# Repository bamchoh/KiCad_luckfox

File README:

# Luckfox Extension Board (KiCad Project)

This repository contains the KiCad project files for the Luckfox extension board. The Luckfox board is an expansion board for the SoB (System on Board) platform.

## Features

- Designed using KiCad.
- Provides 5V power supply via USB port.
- Suitable for expanding the capabilities of the Luckfox SoB.

## Directory Structure

- `.kicad_pcb`, `.kicad_sch`, `.kicad_pro`: Main KiCad project files.
- `production/`: Contains BOM, netlist, positions, and production backups.
- `luckfox-backups/`: Automatic and manual project backups.

## Getting Started

1. Open the project in KiCad.
2. Review the schematic and PCB layout.
3. Use the files in the `production/` directory for manufacturing and assembly.

## License

Please specify your license here.

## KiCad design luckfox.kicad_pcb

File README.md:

# Luckfox Extension Board (KiCad Project)

This repository contains the KiCad project files for the Luckfox extension board. The Luckfox board is an expansion board for the SoB (System on Board) platform.

## Features

- Designed using KiCad.
- Provides 5V power supply via USB port.
- Suitable for expanding the capabilities of the Luckfox SoB.

## Directory Structure

- `.kicad_pcb`, `.kicad_sch`, `.kicad_pro`: Main KiCad project files.

## Getting Started

1. Open the project in KiCad.
2. Review the schematic and PCB layout.

## License

Please specify your license here.

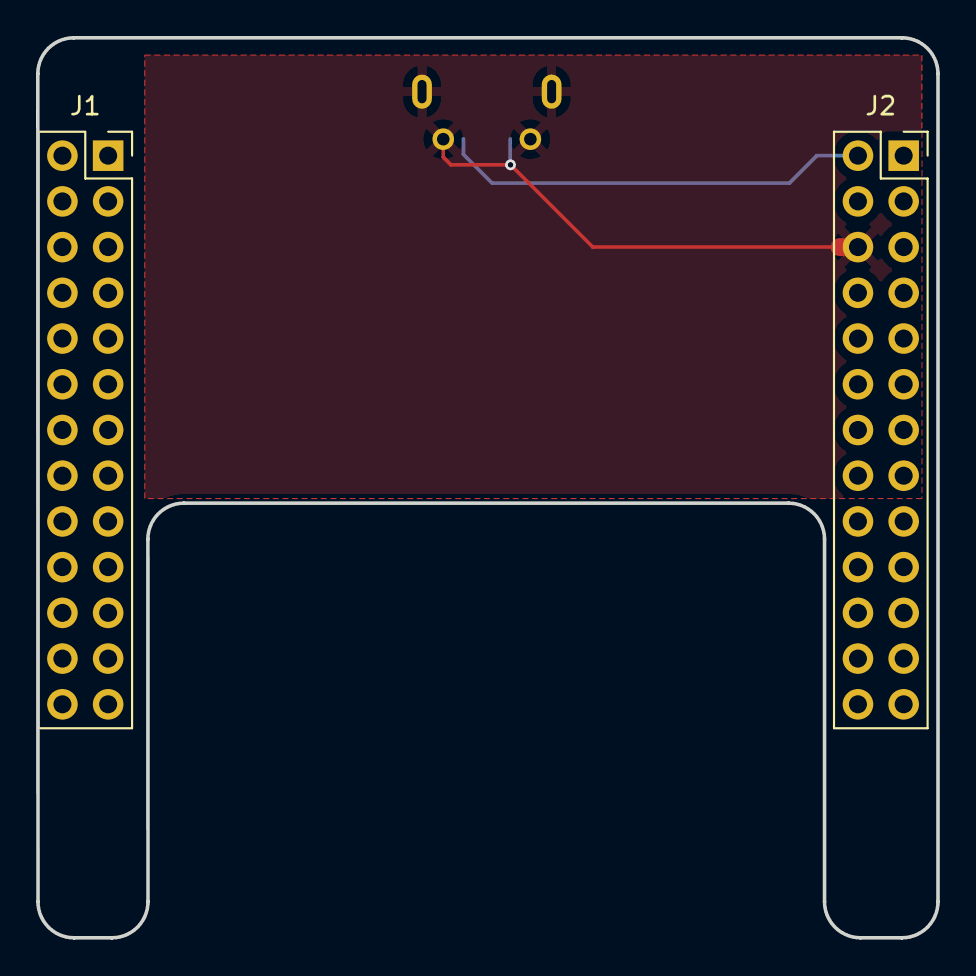
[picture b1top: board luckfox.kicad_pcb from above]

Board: 2 copper layers, 50.0 x 50.0 mm, 3 parts (1 on the bottom side), 2 nets.

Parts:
J1, J2: Conn_02x13_Counter_Clockwise; PinSocket_2x13_P2.54mm_Vertical
USB1: micro USBFemale; MICRO-USB-SMD_5P-P0.65-H-F_C10418

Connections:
unnamed: J2.2, USB1.1 (V+)
unnamed: J2.6, USB1.5 (V-), USB1.SH0 (MTN), USB1.SH1, USB1.SH2, USB1.SH3

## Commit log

2025-06-12 Add English README for Luckfox KiCad project
2025-06-12 Rename README to README.md
